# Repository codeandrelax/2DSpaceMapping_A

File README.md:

# O projektu 🚗
<p align="justify">
Specifikacija projektnog zadatka od strane project owner-a (uopšteni zahtjevi) :
  
- autonomno vozilo
- upravljačka ploča (MCU: PIC24FJ64GAxx)
- lidar
- aplikacija
  
Cilj projektnog zadatka jeste realizacija autonomnog vozila koje ima mogućnost kretanja kroz prostoriju i mapiranje područja oko njega. Vozilo se sastoji od šasije sa 4 točka (2 slobodna točka i 2 točka pogonjena na DC motor) kojima upravlja upravljačka ploča bazirana na mikrokontroleru PIC24FJ64GA. 
</p>
Kao ključni element same ploče, koristimo mikrokontroler iz familije PIC24FJ64GA za upravljanje i kontrolu sistema. Za komunikaciju sa već postojećom pločom koristimo I2C, a za komunikaciju sa drugim periferijama koristimo UART i SPI.
Jedan od glavnih zahtjeva korisnika jeste da se ostvari bežična komunikacija i daljinsko upravljanje samog vozila, za šta je neophodno koristiti WiFi modul koji povezujemo putem UART interfejsa sa mikrokontrolerom.
Mapiranje prostora i kontrola kretanja se vrši uz pomoć Lidara. Korisnik može kontrolisati kretanje vozila pomoću korisničke aplikacije i njenog GUI-a dok prati pogled na prostor u realnom vremenu.
Na kraju, neophodno je razviti PC aolikaciju za prikaz reljefa oko samog vozila. Minimalni uslovi koji moraju biti ispunjeni su mogućnost pokretanja i zaustavljanja vozila.

Nakon prvog sastanka sa project owner-om, dobili smo detaljnije specifikacije samog projektnog zadatka koje podrazumijevaju sljedeće:
- PCB pločica može da bude jednoslojna ili dvoslojna
- prilikom izrade PCB ploče koristimo SMD komponente, gdje je to moguće
- minimalna širina veze prilikom rutiranja iznosi 0.254 mm
- nije potrebno projektovati dodatno napajanje,  dovoljno je koristiti već postojeće
- budžet za narudzbu i kupovinu komponenata ne bi trebalo da prelazi 30 dolara

Početna šema, neophodna za izradu i projektovanje štampane ploče prikazana je na slici ispod, a detaljnije objašnjenje same šeme i načina spajanja iste nalazi se na Wiki stranici.

Nakon projektovane šema, kao rezultat dobijamo PCB i rutiranu pločicu, prikzanu na slici ispod:

Dostavljamo i 3D model PCB-a :

Na slici ispod se nalazi sklopljeno autonomno vozilo sa pratećim komponentama neophodnim za pravilan rad samog vozila.

Demonstracija skeniranja prostora IR senzorom i slanje podataka na aplikaciju za prikaz prostora data je na sledećem snimku.

Demonstracija kretanja vozila pored prepreka data je na sledećem snimku.

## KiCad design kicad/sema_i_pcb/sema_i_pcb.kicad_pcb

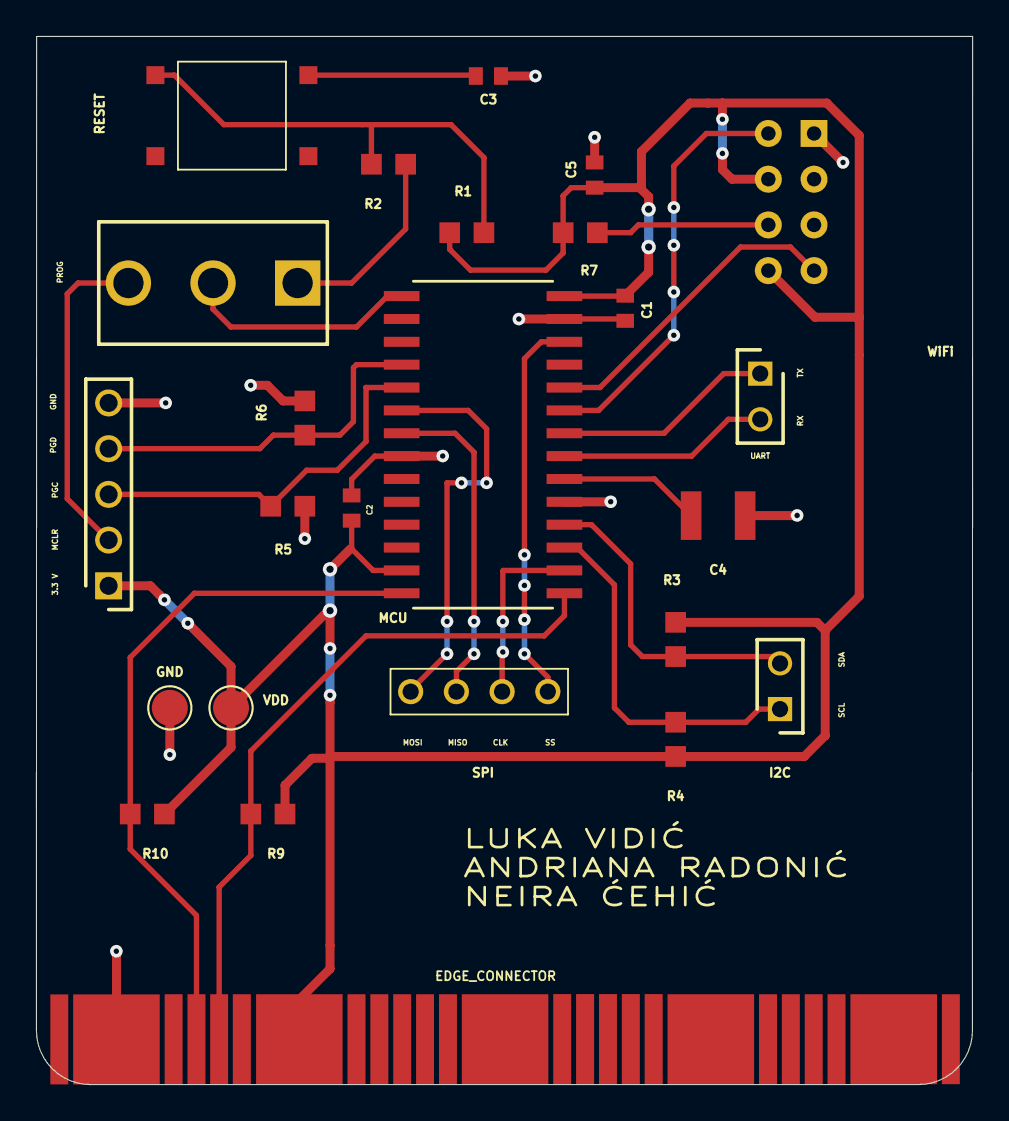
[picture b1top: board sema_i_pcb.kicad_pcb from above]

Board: 2 copper layers, 52.0 x 58.2 mm, 25 parts (0 on the bottom side), 23 nets.

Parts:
C1, C2, C3, C5: 100n; 100nF
C4: 10u; 10uF
EDGE_CONNECTOR: edge_connector
GND: GND; TestPoint_Pad_D2.0mm
I2C: Conn_01x02_Pin; HDRV2W70P0X254_1X2_478X244X884P
MCU: PIC24FJ64GA002-E_SO; SOIC28-W_MC_MCH
PICkit_Conn1: Conn_01x05_Pin; HDRV5W56P0X254_1X5_1240X244X904P
PROG: SW_SPDT; SLW12768644AD
R1, R5, R6, R7: ERA6AEB1020V; 10k
R2: ERA6AEB1020V; 330R
R3, R4, R9, R10: 4.7k; 4k7
RESET: COM-12992; COM12992
SPI: Conn_01x04_Pin; A24PA254DSA71
U2: ESP8266-01_ESP-01; XCVR_ESP8266-01_ESP-01
UART: Conn_01x02_Pin; HDRV2W70P0X254_1X2_478X244X884P
VDD: VCC; TestPoint_Pad_D2.0mm

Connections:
+3.3V: C1.1, C2.1, C5.1, EDGE_CONNECTOR.7 (3.3_V), MCU.13 (VDD), MCU.28 (VDD), PICkit_Conn1.1, R1.1, R3.1, R4.1, R7.1, R9.1, R10.1, U2.6 (EN), U2.8 (VCC), VDD.1
/I2C_SCL: I2C.1, MCU.17 (TCK/RP8/SCL1/CN22/PMD4/RB8), R4.2
/I2C_SDA: I2C.2, MCU.18 (TDO/RP9/SDA1/CN21/PMD3/RB9), R3.2
/MCLR: MCU.1 (~MCLR), PROG.2 (B)
/PGC: MCU.5 (PGC1/EMUC1/AN3/C2IN+/RP1/CN5/RB1), PICkit_Conn1.3, R5.1
/PGD: MCU.4 (PGD1/EMUD1/AN2/C2IN-/RP0/CN4/RB0), PICkit_Conn1.4, R6.1
/SCL_MBIT: EDGE_CONNECTOR.5 (SCL), MCU.15 (PGC3/EMUC3/RP6/ASCL1/CN24/PMD6/RB6), R9.2
/SDA_MBIT: EDGE_CONNECTOR.4 (SDA), MCU.14 (PGD3/EMUD3/RP5/ASDA1/CN27/PMD7/RB5), R10.2
/SPI_CLK: MCU.16 (RP7/INT0/CN23/PMD5/RB7), SPI.3
/SPI_DI: MCU.7 (AN5/C1IN+/RP3/SCL2/CN7/RB3), SPI.2
/SPI_DO: MCU.6 (AN4/C1IN-/RP2/SDA2/CN6/RB2), SPI.1
/SPI_SS: MCU.26 (AN9/RP15/CN11/PMCS1/RB15), SPI.4
/THROW_PROG: PICkit_Conn1.2, PROG.3 (C)
/THROW_RST: PROG.1 (A), R2.2
/UART_RX: MCU.21 (PGD2/EMUD2/TDI/RP10/CN16/PMD2/RB10), UART.2
/UART_RX_WIFI: MCU.24 (AN11/RP13/CN13/PMRD/RB13), U2.4 (RXD)
/UART_TX: MCU.22 (PGC2/EMUC2/TMS/RP11/CN15/PMD1/RB11), UART.1
/UART_TX_WIFI: MCU.23 (AN12/RP12/CN14/PMD0/RB12), U2.5 (TXD)
GND: C1.2, C2.2, C3.2, C4.2, C5.2, EDGE_CONNECTOR.2 (GND), GND.1, MCU.8 (VSS), MCU.19 (DISVREG), MCU.27 (VSS), PICkit_Conn1.5, R5.2, R6.2, U2.1 (GND)
unnamed: C3.1, RESET.B1
unnamed: R1.2, R2.1, RESET.A1
unnamed: C4.1, MCU.20 (VCAP/VDDCORE)
unnamed: R7.2, U2.7 (~RST)

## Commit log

2024-01-15 Issue #4 : Projektovanje elektricne seme
    - Dodana planirana sema
    - Dodani modeli za mikrokontroler i esp8266
2024-01-16 Issue #4 : Planiranje projektovanja električne šeme
    - Modifikovani folderi tako da se obezbjedi laksi uvoz modela
    - Modifikovana sema da se omoguci programiranje flash memorije
    - Dodatne izmjene na semi
2024-01-17 Issue #4 : Planiranje projektovanja električne šeme
    - Dodan dio za napajanje, sa DC/DC pretvaračem
2024-01-18 Issue #4 : Planiranje projektovanja električne šeme
    - Reorganizovana šema i izvršena ERC provjera
2024-01-22 Issue #4 : Projektovanje električne šeme
    - Uklonjen dio sa DC/DC pretvaračem zbog napajanja sa postojeće ploče
    - Dodan sprežni kondezator između napajanja i mase kod WiFi modula
    - Umjesto jumpera ubačen taster kod kola za reset MCRL pina
    - Dodatne modifikacije i poboljšanja
2024-01-22 Issue #6 : Sastavljanje liste komponenata i pitanja
    - dodana pitanja i lista komponenata
2024-01-23 Issue #9 : Kreiranje simbola i modela za Edge Connector Dodan simbol za Edge Connector
2024-01-23 Issue #9 : Kreiranje simbola i modela za Edge Connector Dodan footprint za Edge Connector
2024-01-24 Issue #9 : Kreiranje simbola i modela za Edge Connector
    - Izmjenjen footprint edge connector-a
2024-01-25 Issue #6 : Sastavljanje liste komponenata i pitanja Dodano novo pitanje
2024-01-25 Issue #9 : Kreiranje simbola i modela za Edge Connector
    - Izmjene u footprint-u edge connector-a
2024-01-25 Issue #9 : Kreiranje simbola i modela za Edge Connector
    - Modifikovan footprint edge connector-a
2024-01-25 Issue #3 : Odabir komponenata štampane ploče
    - Odabrane sve potrebne komponente
    - Dodan .csv fajl sa komponentama i linkovima do kataloga
    - Skupljeni svi otisci i modeli potrebni za PCB
2024-01-25 Issue #3 : Odabir komponenata štampane ploče
    - Promjenjen odabir za 10k i 4.7k otpornike
    - Ažurirane promjene otisaka i modela u projektu
2024-01-25 Issue #4 : Projektovanje električne šeme
    - Promjena na šemi, nakon dodatnog čitanja datasheet-a zaključeno je da RST pin WiFi modula mora biti pull-up otpornikom spojen na +3.3V umjesto direktno
    - Novi otpornik dodat u .csv fajl
2024-01-26 Issue #7 : Raspored komponenata na PCB
    - Dodana kompletirana šema , spremna za rutiranje.
2024-01-26 Issue #8 : Rutiranje komponenata na PCB - Dodana rutirana šema
2024-01-26 Globalne izmjene:
    - Promjenjena odabrana komponenta 10uF kondenzatora
    - Ažurirani otisak i 3D model novog kondenzatora
    - Popravljene greške u PCB u vezi sa silkscreen-om i zaostalim vezama
    - Izmjene silkscreen-a na drugim otiscima komponenti
    - Blage dorade u dizajnu štampane ploče
2024-01-26 Globalna izmjena:
    - Novoodabrana komponenta 10uF kondenzatora ažurirana u .csv fajlu
2024-02-23 Update komponente.csv
    Ispravljeni serijski brojevi
2024-02-23 Issue #11 : Dodavanje dokumentacije
    - Dodana dokumentacija šeme i PCB-a u folder docs
2024-03-19 Issue #16 : Provjeriti mogućnosti implementacije simulatora LIDAR-a
    Dodan izvorni kod koji implementira simulator mobilnog robota sa lidar senzorom koji razmjenjuje mjerne podatke putem WiFi sa glavnim programom
2024-03-19 Issue #16 : Provjeriti mogućnosti implementacije simulatora LIDAR-a
    Obrisani nepotrebni fajlovi
2024-03-19 Issue #12 : Implentacija wireless komunikacije, Issue #14 Implementirati algoritam iscrtavanja
    - dodan izvorni kod koji obuhvata rijesenje navedena dva taska
2024-03-21 Issue #15 : Implementirati upravljanje kretanja kroz aplikaciju
    - Dodan mehanizam za START/STOP kontrolu kretanja
    - Implementiran način komunikacije datih događaja
    - Male izmjene na GUI ekranu
2024-03-28 Dodan .gitignore za mikroC projekte
2024-03-28 Issue #20 : Testiranje i programiranje stampane ploče pomoću programatora
    - Dodan blinky primjer koji testira rad ploče i programiranje
2024-03-28 Issue #20 : Testiranje i programiranje stampane ploče pomoću programatora
    Bug fix
2024-04-02 Issue #24 : Osposobljavanje servo motora
    - Dodan testni firmware kod koji okreće servo motor od 0 do 180 stepeni i nazad kontinualno
2024-04-02 Issue #22 : Osposobljavanje IR distance click senzora - Dodan kod za provjeru IR distance senzora.
2024-04-04 Issue #28 : Modifikacija aplikacije za mapiranje prostora
    - Izmjenjena aplikacija tako da se prilagodi podacima koji dolaze sa stvarnog sistema
    - Zadržane funkcionalnosti i prilikom rada sa simulatorom
2024-04-15 Issue #27 : Integracija servo motora i IR senzora
    - Dodan incijalni kod za radar koji salje podatke preko UART komunikacije na PC racunar
2024-04-17 Issue #26 : Osposobljavanje komunikacije sa postojećom pločom - Dodan kod za testiranje tockova.
2024-04-20 Issue #30 : Integracija i osposobljavanje sistema
    - Dodan kod koji omogućava kretanje vozila kao i detekciju i izbjegavanje prepreka
2024-04-20 Issue #30 : Integracija i osposobljavanje sistema
    - Dokumentovani svi izvorni fajlovi sa doxygen i obicnim komentarima
2024-04-25 Issue #30 : Integracija i osposobljavanje sistema
    - Modikovana logika kretanja
2024-04-25 Issue #25 : Implementacija WiFi komunikacije
2024-04-26 Issue #30 : Integracija i osposobljavanje sistema
    - Modifikovana logika kretanja, sada je kretanje dosta bolje
2024-04-30 Issue #25 : Implementacija WiFi komunikacije
    - Dodan kod koji implementira WiFi komunikaciju putem esp8266 modula
    - Unutar koda je dodatni kod za debagovanje putem UART-USB konvertera
2024-05-09 Issue #31 : Modifikacija softverskih aplikacija
    - Aplikacija za iscrtavanje prostora razdvojena na dvije kako je i opisano
    - U aplikaciji za simulator obrisane nepotrebe funkcionalnosti
2024-05-09 Issue #30 : Integracija i osposobljavanje sistema
    - Integrisane funkcionalnosti radara i WiFi prenosa podataka u svrhu testiranja rada sa aplikacijom za iscrtavanje prostora
2024-05-09 Issue #31 : Modifikacija softverskih aplikacija
    - Uklonjeno još nepotrebnih funkcionalnosti iz simulator aplikacije
2024-05-09 Issue #31 : Modifikacija softverskih aplikacija:
    - Implementirana logika za detekciju pritiska START i STOP tastera
    - Modifikovana logika iscrtavanja tako da se bolje prilagodi manjem broju tačaka koje se mogu ostvariti trenutnim sistemom
2024-05-09 Issue #30 : Integracija i osposobljavanje sistema
    - Implementirana funkcionalnost koja testira mogucnost START/STOP detekcije i odgovarajuce akcije
    - Dodatna poboljsanja
2024-05-10 Issue #31 : Modifikacija softverskih aplikacija
    - Popravljeni bagovi i poboljsan kod
2024-05-10 Issue #30 : Integracija i osposobljavanje sistema
    - Popravljeni bagovi koji vode sistem u nestabilno stanje nakon stop-start sekvence
    - Kompletirana integracija radara i WiFi komunikacije
2024-05-10 Issue #30 : Integracija i osposobljavanje sistema
    - Ispravke u podesavanju projekta
2024-05-11 Issue #33 : Osposobljavanje i testiranje ultrazvučnog senzora
    - Dodan kod biblioteke koja upravlja radom HC-SR04 senzora
    - Dodan izvorni kod glavnog programa koji testira rad biblioteke i senzora tako što dobijene udaljenosti proslijeđuje na UART serijski izlaz
2024-05-14 Issue #30 : Integracija i osposobljavanje sistema
    - Dodane finalne izmjene i pokušaj konačne integracije sistema
2024-05-17 Dodana video prezentacija
